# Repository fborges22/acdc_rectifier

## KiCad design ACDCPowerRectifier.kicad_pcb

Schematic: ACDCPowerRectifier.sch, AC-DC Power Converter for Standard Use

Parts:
C1, C2, C3, C4, C5, C6: 1000uF; C_Radial_D35_L51_P10
D1: 10A; Diode_Bridge_18.5x5.5
P1: INPUT; Pin_Header_Angled_1x02
P2: AC1; Banana_Jack_1Pin
P3: AC2; Banana_Jack_1Pin
P4: DCPOS; Banana_Jack_1Pin
P5: DCNEG; Banana_Jack_1Pin
P6: DCCT; Banana_Jack_1Pin
R1, R2: 180; Resistor_Horizontal_RM10mm
R3: 10; Resistor_Vertical_RM5mm
R4, R5: 100k; Resistor_Horizontal_RM10mm
U1: MOC3020M; DIP-6_W7.62mm_LongPads
U2: BT139-800; TO-220_Neutral123_Vertical

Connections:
GND: P1.1, U1.2
unnamed: C1.1, C3.1, C5.1, D1.3 (+), P4.1, R4.2
unnamed: C1.2, C2.1, C3.2, C4.1, C5.2, C6.1, P6.1, R4.1, R5.2
unnamed: C2.2, C4.2, C6.2, D1.1 (-), P5.1, R5.1
unnamed: D1.2, P3.1
unnamed: D1.4, R2.1, R3.1, U2.2
unnamed: P1.2, R1.2
unnamed: P2.1, R3.2, U2.1
unnamed: R1.1, U1.1
unnamed: R2.2, U1.6
unnamed: U1.4, U2.3

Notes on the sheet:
AC-DC Standard Full Bridge Rectifier System
* All output capacitors should be electrolytic of 1000uF@250V
* All resistors should be 1/2 EXCEPT the INRUSH LIMITER (R3) 5W
* The P1 connector will be connected to an 5V based microcontroller

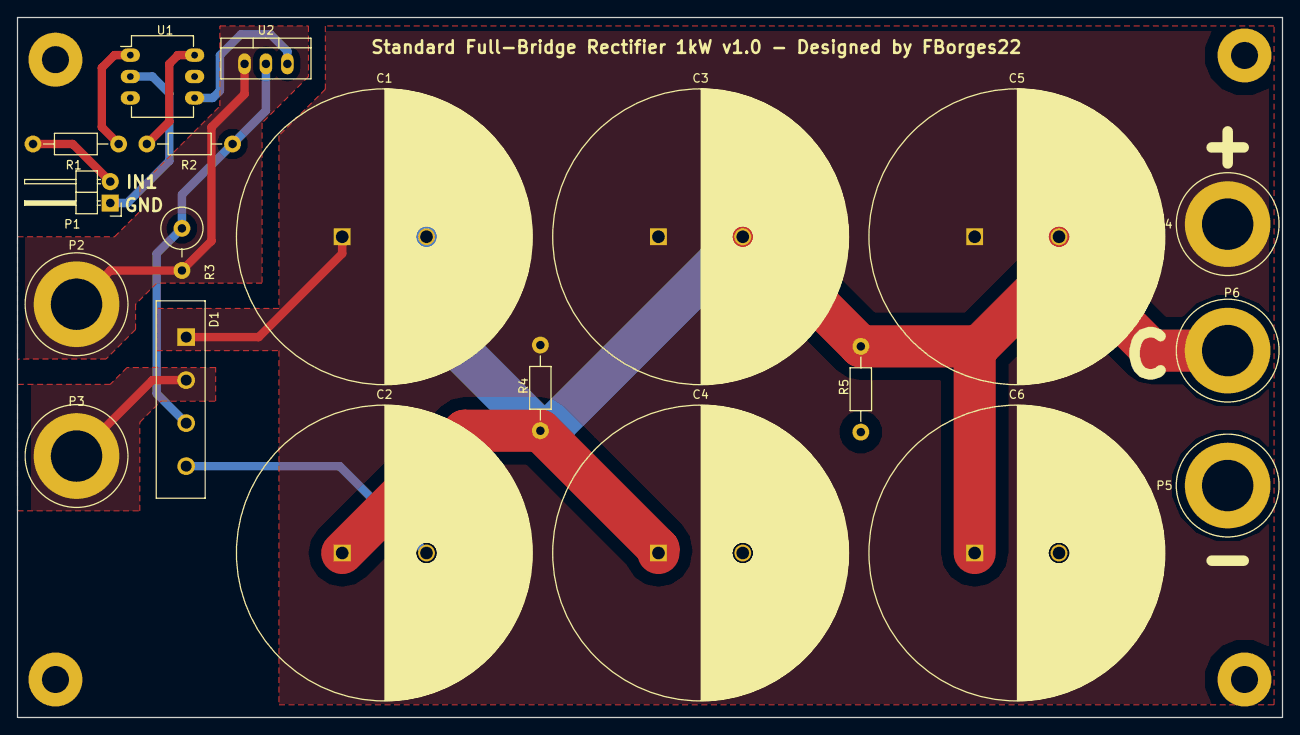
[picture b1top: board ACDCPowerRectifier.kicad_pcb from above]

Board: 2 copper layers, 150.0 x 83.0 mm, 24 parts (0 on the bottom side), 11 nets.

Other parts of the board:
MH1, MH2, MH3, MH4: MountingHole_3.2mm_M3_Pad

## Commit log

2019-02-04 First commit of the AC-DC converter circuit
